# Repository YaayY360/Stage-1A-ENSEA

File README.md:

# Stage-1A-ENSEA
Project de gestion d'inventaire avec un lecteur de tag RFID et de la gestion de base de données

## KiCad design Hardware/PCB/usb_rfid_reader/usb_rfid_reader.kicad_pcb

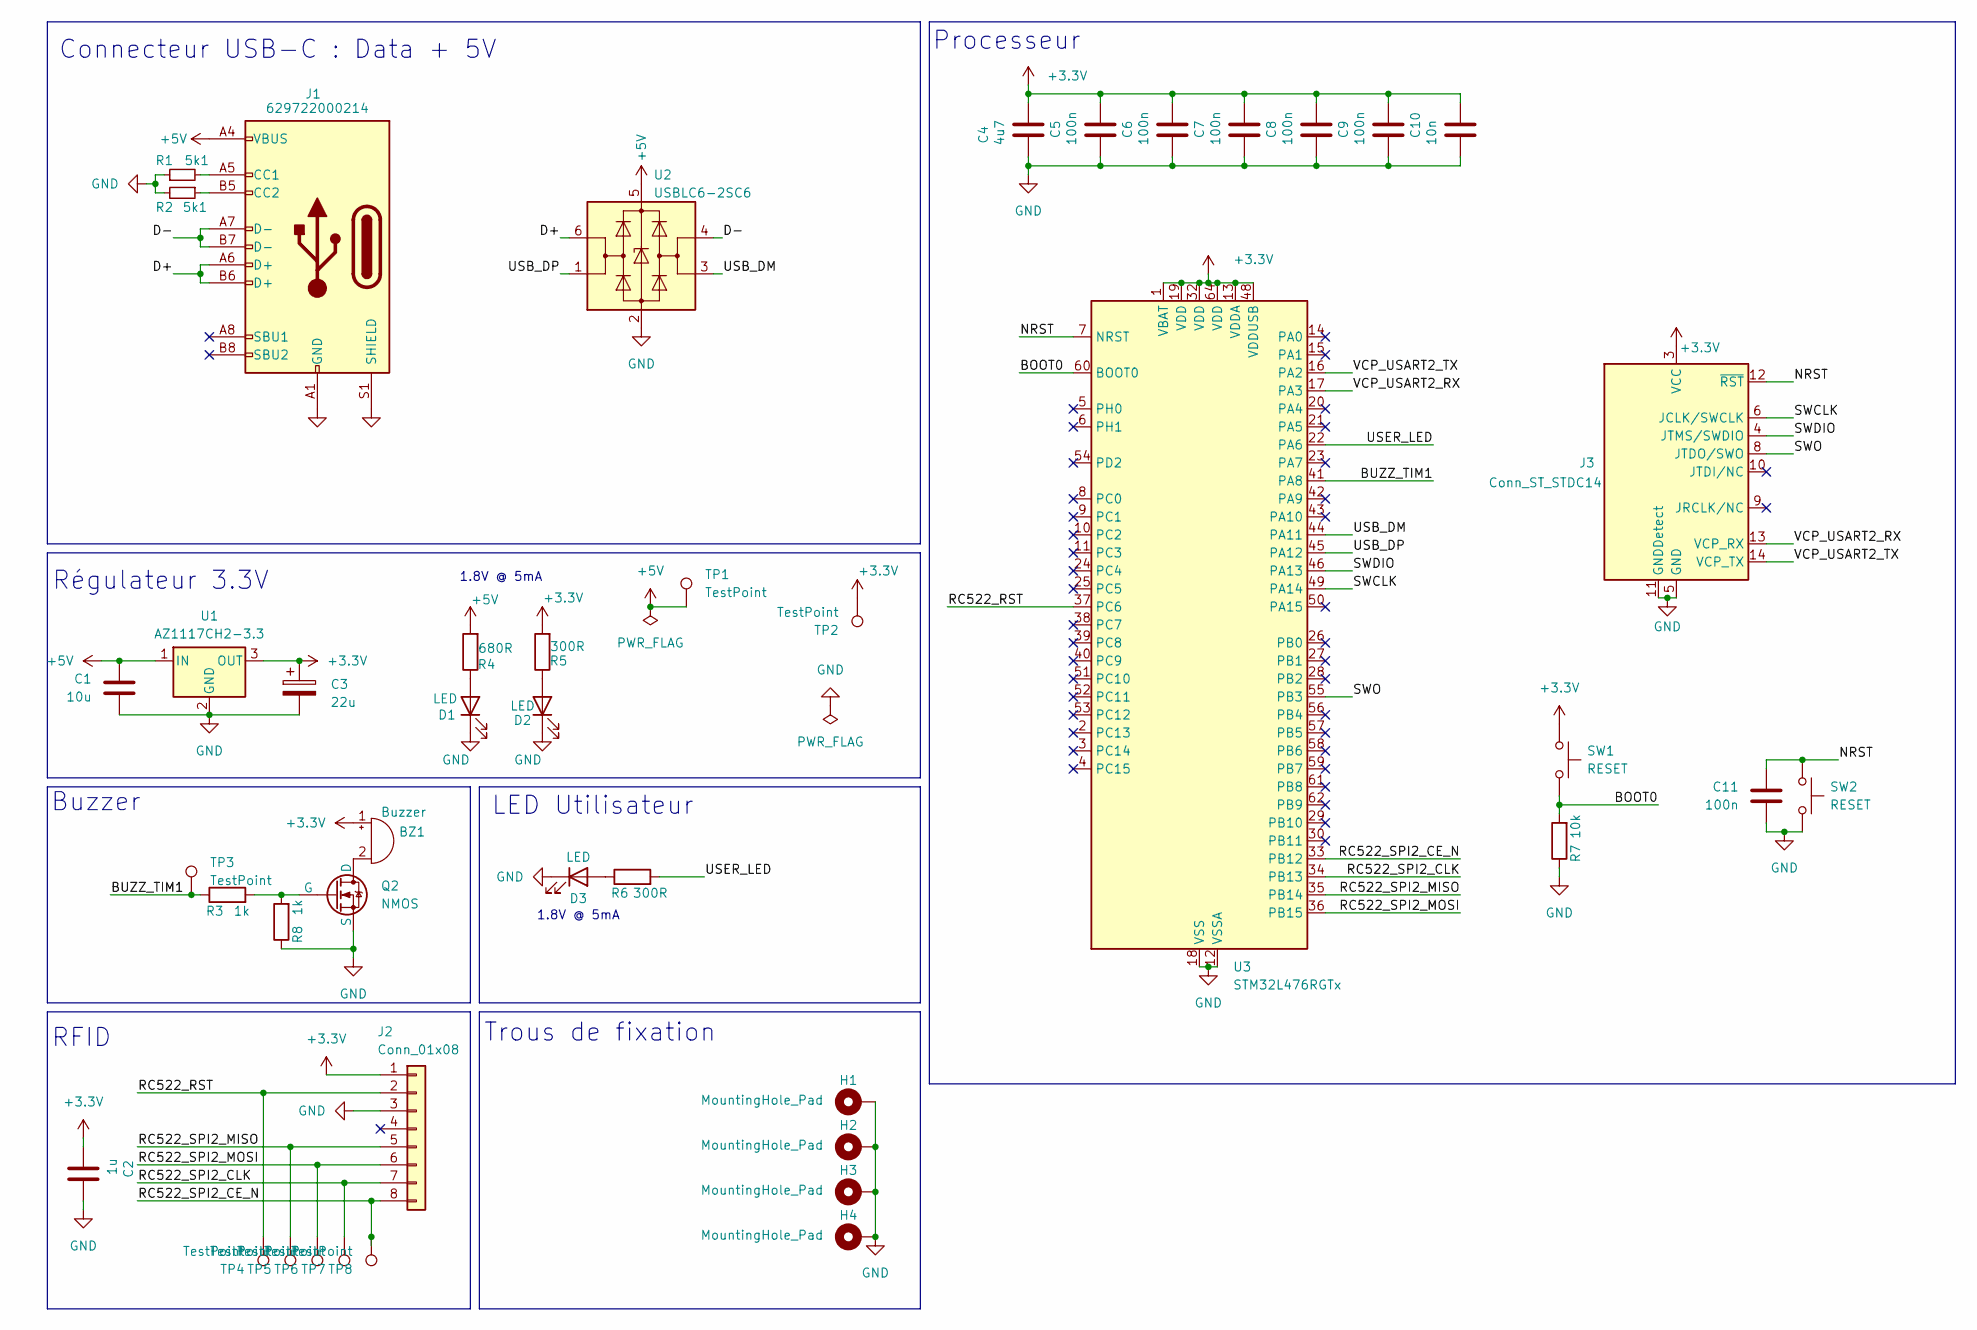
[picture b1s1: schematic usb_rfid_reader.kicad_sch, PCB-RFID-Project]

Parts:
BZ1: Buzzer; Buzzer_D14mm_H7mm_P10mm; MPN PS1420P02CT
C1: 10u; C_0603_1608Metric; MPN 885012106031
C2: 1u; C_0603_1608Metric; MPN GRM188R61A475KE15D
C3: 22u; CP_Elec_5x5.4; MPN 865060442002
C4: 4u7; C_0603_1608Metric; MPN GRM188R61A475KE15D
C5, C6, C7, C8, C9, C11: 100n; C_0603_1608Metric; MPN GRM188R71C104KA01D
C10: 10n; C_0603_1608Metric; MPN GRM188R71C104KA01D
D1, D2, D3: LED; LED_0603_1608Metric; MPN 150060RS55040
H1, H2, H3, H4: MountingHole_Pad; MountingHole_3.2mm_M3_DIN965_Pad
J1: 629722000214; USB_C_Receptacle_HRO_TYPE-C-31-M-12; MPN WE 629722000214
J2: Conn_01x08; MODULE_CEG006900; MPN 61300811121
J3: Conn_ST_STDC14; PinHeader_2x07_P1.27mm_Vertical_SMD; MPN STDC14
Q2: NMOS; SOT-23-3; MPN SQ2310ES-T1_BE3
R1, R2: 5k1; R_0402_1005Metric
R3, R8: 1k; R_0603_1608Metric; MPN RC0603FR-071KL
R4: 680R; R_0603_1608Metric; MPN RC0603FR-073KL
R5, R6: 300R; R_0603_1608Metric; MPN RC0603FR-071K5L
R7: 10k; R_0603_1608Metric; MPN RC0603FR-0710KL
SW1, SW2: RESET; SW_SPST_PTS645Sx43SMTR92; MPN PTS645SK43SMTR92 LFS
TP1, TP2, TP3, TP4, TP5, TP6, TP7, TP8: TestPoint; TestPoint_Pad_D1.0mm
U1: AZ1117CH2-3.3; SOT-223-3_TabPin2; MPN AZ1117CH2-3.3TRG1
U2: USBLC6-2SC6; SOT-23-6; MPN USBLC6-2SC6
U3: STM32L476RGTx; LQFP-64_10x10mm_P0.5mm; MPN STM32L476RGT6

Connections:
+3.3V: BZ1.1 (+), C2.1, C3.1, C4.2, C5.2, C6.2, C7.2, C8.2, C9.2, C10.2, J2.1, J3.3 (VCC), R5.2, SW1.1, TP2.1, U1.3 (OUT), U3.1 (VBAT), U3.13 (VDDA), U3.19 (VDD), U3.32 (VDD), U3.48 (VDDUSB), U3.64 (VDD)
+5V: C1.1, J1.A4 (VBUS), J1.A9 (VBUS), J1.B4 (VBUS), J1.B9 (VBUS), R4.2, TP1.1, U1.1 (IN), U2.5 (VBUS)
/BOOT0: R7.2, SW1.2, U3.60 (BOOT0)
/BUZZ_TIM1: R3.1, TP3.1, U3.41 (PA8)
/D+: J1.A6 (D+), J1.B6 (D+), U2.6 (I/O1)
/D-: J1.A7 (D-), J1.B7 (D-), U2.4 (I/O2)
/NRST: C11.1, J3.12 (~RST), SW2.1, U3.7 (NRST)
/RC522_RST: J2.2, TP4.1, U3.37 (PC6)
/RC522_SPI2_CE_N: J2.8, TP8.1, U3.33 (PB12)
/RC522_SPI2_CLK: J2.7, TP7.1, U3.34 (PB13)
/RC522_SPI2_MISO: J2.5, TP5.1, U3.35 (PB14)
/RC522_SPI2_MOSI: J2.6, TP6.1, U3.36 (PB15)
/SWCLK: J3.6 (JCLK/SWCLK), U3.49 (PA14)
/SWDIO: J3.4 (JTMS/SWDIO), U3.46 (PA13)
/SWO: J3.8 (JTDO/SWO), U3.55 (PB3)
/USB_DM: U2.3 (I/O2), U3.44 (PA11)
/USB_DP: U2.1 (I/O1), U3.45 (PA12)
/USER_LED: R6.2, U3.22 (PA6)
/VCP_USART2_RX: J3.13 (VCP_RX), U3.17 (PA3)
/VCP_USART2_TX: J3.14 (VCP_TX), U3.16 (PA2)
GND: C1.2, C2.2, C3.2, C4.1, C5.1, C6.1, C7.1, C8.1, C9.1, C10.1, C11.2, D1.1 (K), D2.1 (K), D3.1 (K), H1.1, H2.1, H3.1, H4.1, J1.A1 (GND), J1.A12 (GND), J1.B1 (GND), J1.B12 (GND), J1.S1 (SHIELD), J2.3, J3.5 (GND), J3.7 (GND), J3.11 (GNDDetect), Q2.3 (S), R1.1, R2.2, R7.1, R8.1, SW2.2, U1.2 (GND), U2.2 (GND), U3.12 (VSSA), U3.18 (VSS), U3.31 (VSS), U3.47 (VSS), U3.63 (VSS)
unnamed: BZ1.2 (-), Q2.1 (D)
unnamed: D1.2 (A), R4.1
unnamed: D2.2 (A), R5.1
unnamed: D3.2 (A), R6.1
unnamed: J1.A5 (CC1), R1.2
unnamed: J1.B5 (CC2), R2.1
unnamed: Q2.2 (G), R3.2, R8.2

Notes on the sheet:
1.8V @ 5mA
Processeur
LED Utilisateur
RFID
Trous de fixation
Régulateur 3.3V
Buzzer
Connecteur USB-C : Data + 5V

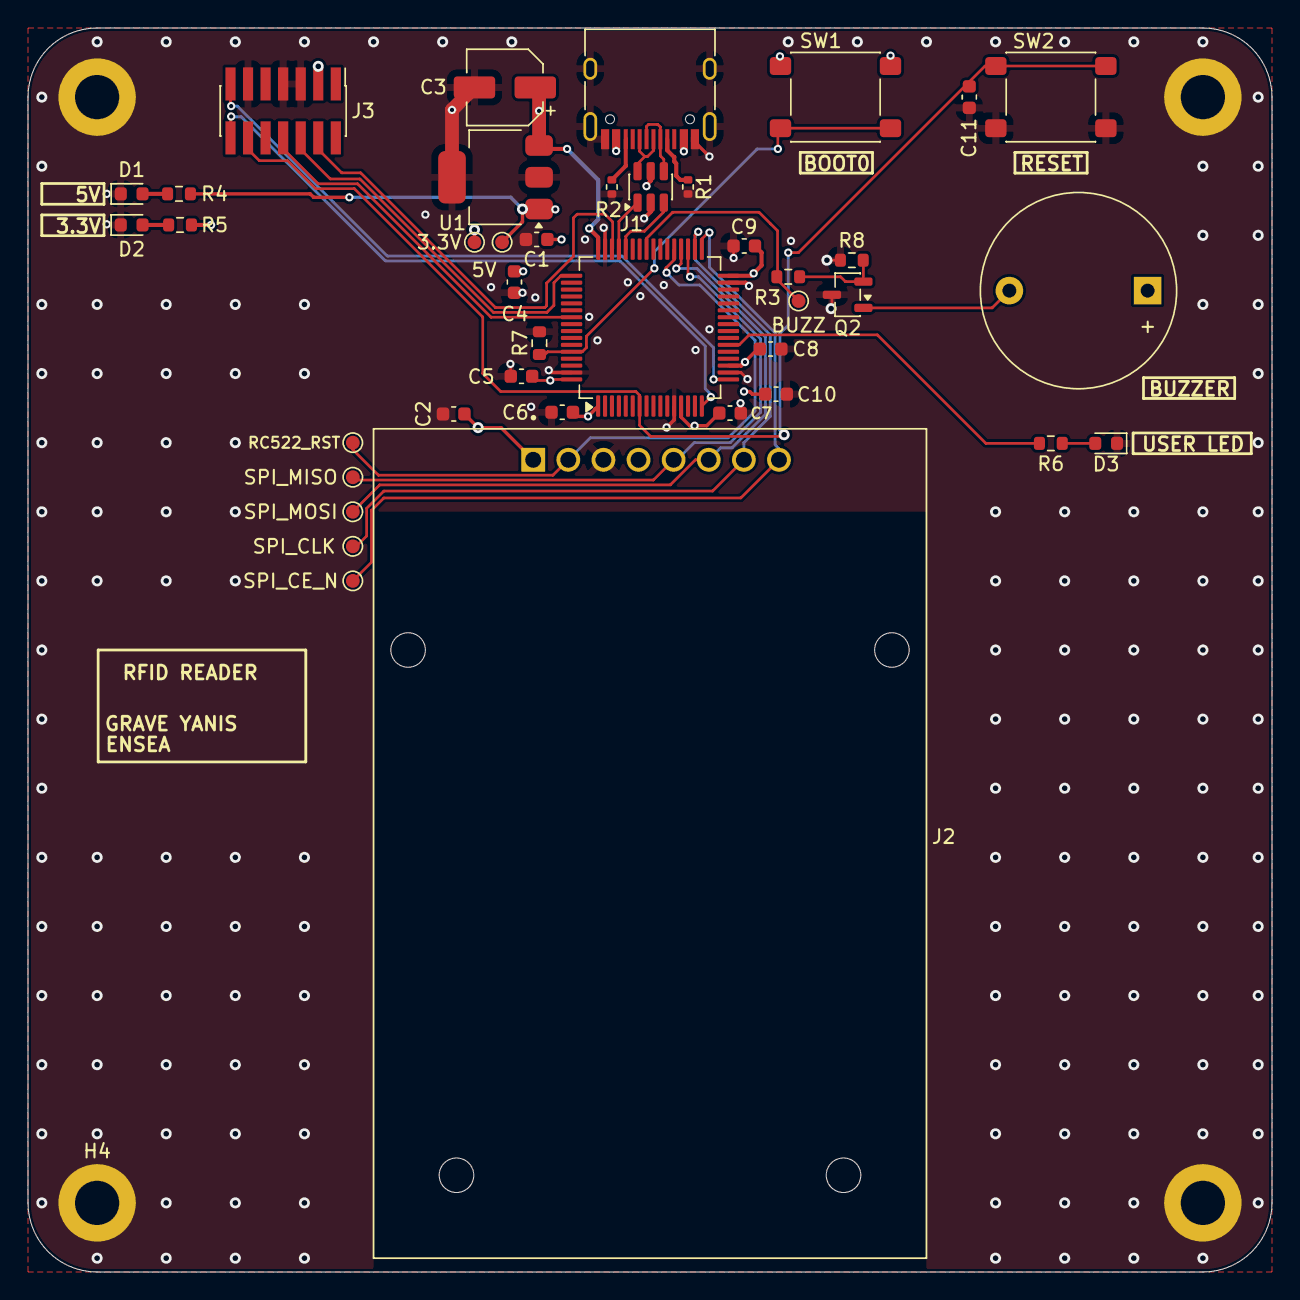
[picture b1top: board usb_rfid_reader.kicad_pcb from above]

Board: 4 copper layers, 90.0 x 90.0 mm, 44 parts (0 on the bottom side), 28 nets.

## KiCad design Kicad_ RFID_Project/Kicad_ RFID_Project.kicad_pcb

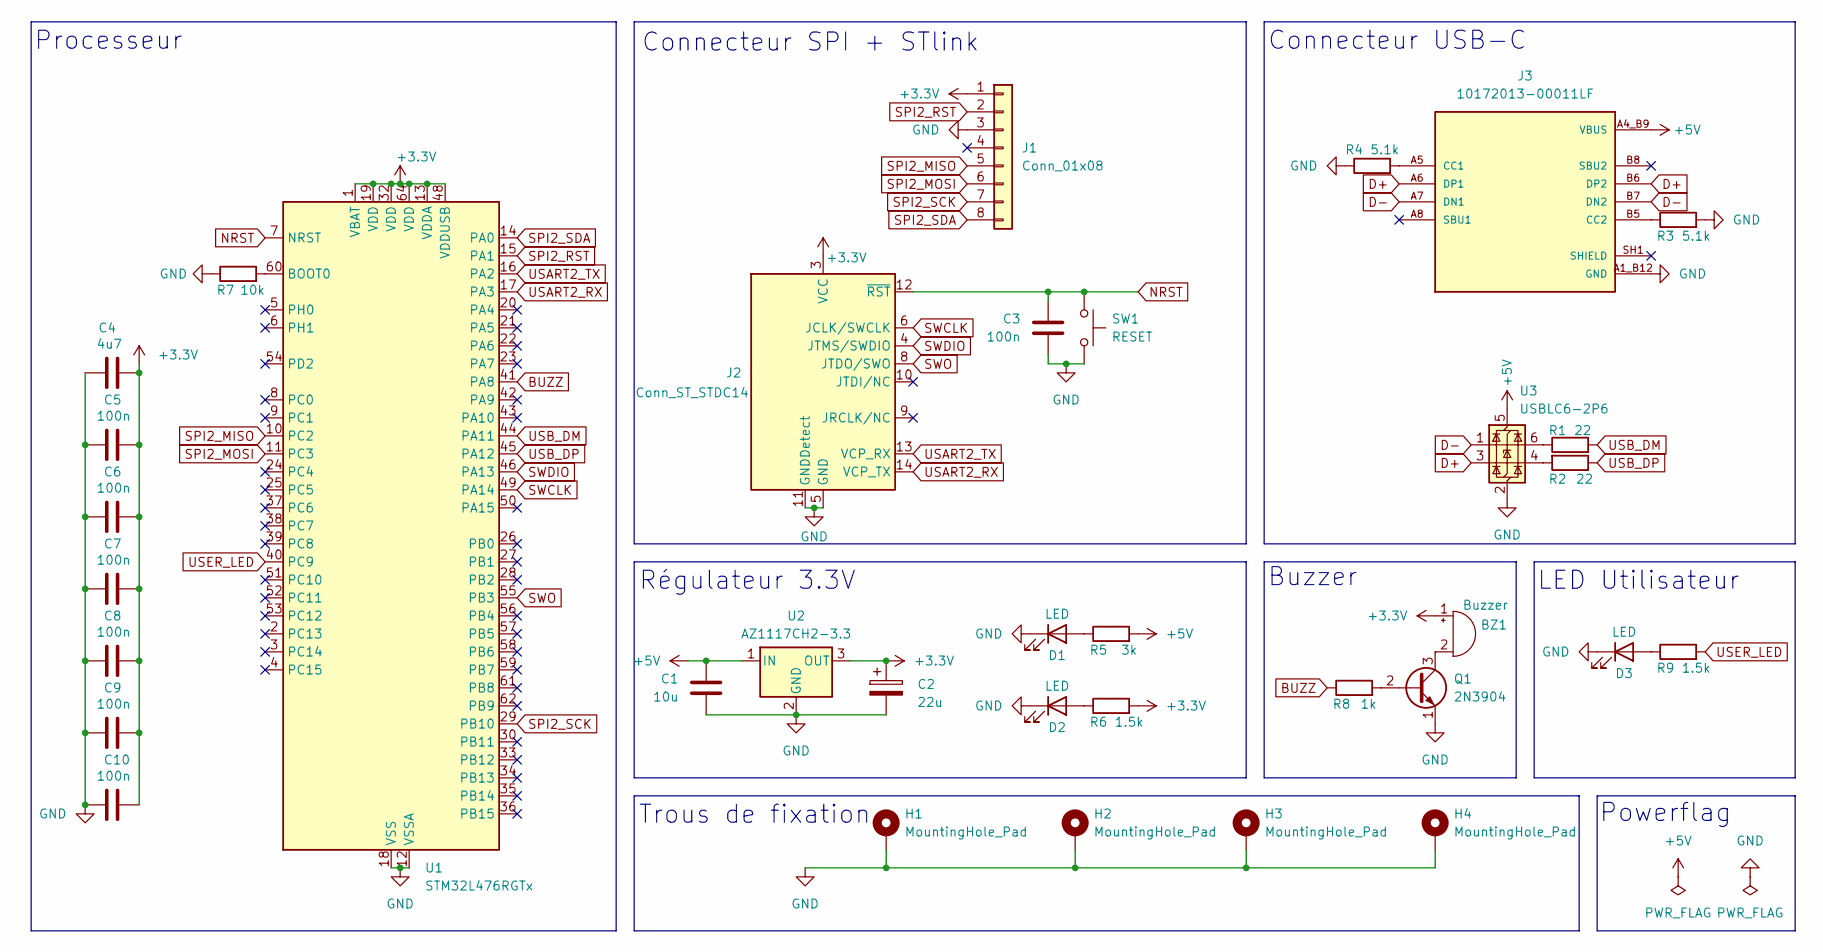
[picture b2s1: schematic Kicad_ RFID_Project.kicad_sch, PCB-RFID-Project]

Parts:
BZ1: Buzzer; Buzzer_D14mm_H7mm_P10mm; MPN PS1420P02CT
C1: 10u; C_0603_1608Metric; MPN GRM188R61A106KE69D
C2: 22u; CP_Elec_5x5.4; MPN GRM21BR61A226ME44L
C3, C5, C6, C7, C8, C9, C10: 100n; C_0603_1608Metric; MPN GRM188R71C104KA01D
C4: 4u7; C_0603_1608Metric; MPN GRM188R61A475KE15D
D1, D2, D3: LED; LED_0603_1608Metric; MPN 150060RS75000
H1, H2, H3, H4: MountingHole_Pad; MountingHole_3.2mm_M3_DIN965_Pad
J1: Conn_01x08; MODULE_CEG006900; MPN 61300811121
J2: Conn_ST_STDC14; PinHeader_2x07_P1.27mm_Vertical_SMD; MPN STDC14
J3: 10172013-00011LF; AMPHENOL_10172013-00011LF; PARTREV A
Q1: 2N3904; TO-92_Inline; MPN 2N3904BU
R1, R2: 22; R_0603_1608Metric; MPN RC0603FR-0722RL
R3, R4: 5.1k; R_0603_1608Metric; MPN RC0603FR-0722RL
R5: 3k; R_0603_1608Metric; MPN RC0603FR-073KL
R6, R9: 1.5k; R_0603_1608Metric; MPN RC0603FR-071K5L
R7: 10k; R_0603_1608Metric; MPN RC0603FR-0710KL
R8: 1k; R_0603_1608Metric; MPN RC0603FR-071KL
SW1: RESET; SW_SPST_PTS645Sx43SMTR92; MPN PTS645SK43SMTR92 LFS
U1: STM32L476RGTx; LQFP-64_10x10mm_P0.5mm; MPN STM32L476RGT6
U2: AZ1117CH2-3.3; SOT-223-3_TabPin2; MPN AZ1117CH2-3.3TRG1
U3: USBLC6-2P6; SOT-666; MPN USBLC6-2P6

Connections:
+3.3V: BZ1.1 (+), C2.1, C4.2, C5.2, C6.2, C7.2, C8.2, C9.2, C10.2, J1.1, J2.3 (VCC), R6.2, U1.1 (VBAT), U1.13 (VDDA), U1.19 (VDD), U1.32 (VDD), U1.48 (VDDUSB), U1.64 (VDD), U2.3 (OUT)
+5V: C1.1, J3.A4_B9 (VBUS), J3.A9_B4 (VBUS), R5.2, U2.1 (IN), U3.5 (VBUS)
BUZZ: R8.1, U1.41 (PA8)
D+: J3.A6 (DP1), J3.B6 (DP2), U3.3 (I/O2)
D-: J3.A7 (DN1), J3.B7 (DN2), U3.1 (I/O1)
GND: C1.2, C2.2, C3.2, C4.1, C5.1, C6.1, C7.1, C8.1, C9.1, C10.1, D1.1 (K), D2.1 (K), D3.1 (K), H1.1, H2.1, H3.1, H4.1, J1.3, J2.5 (GND), J2.7 (GND), J2.11 (GNDDetect), J3.A1_B12 (GND), J3.A12_B1 (GND), Q1.1 (E), R3.2, R4.1, R7.1, SW1.2, U1.12 (VSSA), U1.18 (VSS), U1.31 (VSS), U1.47 (VSS), U1.63 (VSS), U2.2 (GND), U3.2 (GND)
NRST: C3.1, J2.12 (~RST), SW1.1, U1.7 (NRST)
unnamed: BZ1.2 (-), Q1.3 (C)
unnamed: D1.2 (A), R5.1
unnamed: D2.2 (A), R6.1
unnamed: D3.2 (A), R9.1
unnamed: J3.A5 (CC1), R4.2
unnamed: J3.B5 (CC2), R3.1
unnamed: Q1.2 (B), R8.2
unnamed: R1.1, U3.6 (I/O1)
unnamed: R2.2, U3.4 (I/O2)
unnamed: R7.2, U1.60 (BOOT0)
SPI2_MISO: J1.5, U1.10 (PC2)
SPI2_MOSI: J1.6, U1.11 (PC3)
SPI2_RST: J1.2, U1.15 (PA1)
SPI2_SCK: J1.7, U1.29 (PB10)
SPI2_SDA: J1.8, U1.14 (PA0)
SWCLK: J2.6 (JCLK/SWCLK), U1.49 (PA14)
SWDIO: J2.4 (JTMS/SWDIO), U1.46 (PA13)
SWO: J2.8 (JTDO/SWO), U1.55 (PB3)
USART2_RX: J2.14 (VCP_TX), U1.17 (PA3)
USART2_TX: J2.13 (VCP_RX), U1.16 (PA2)
USB_DM: R1.2, U1.44 (PA11)
USB_DP: R2.1, U1.45 (PA12)
USER_LED: R9.2, U1.40 (PC9)

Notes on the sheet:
Processeur
LED Utilisateur
Powerflag
Régulateur 3.3V
Connecteur SPI + STlink
Trous de fixation
Buzzer
Connecteur USB-C

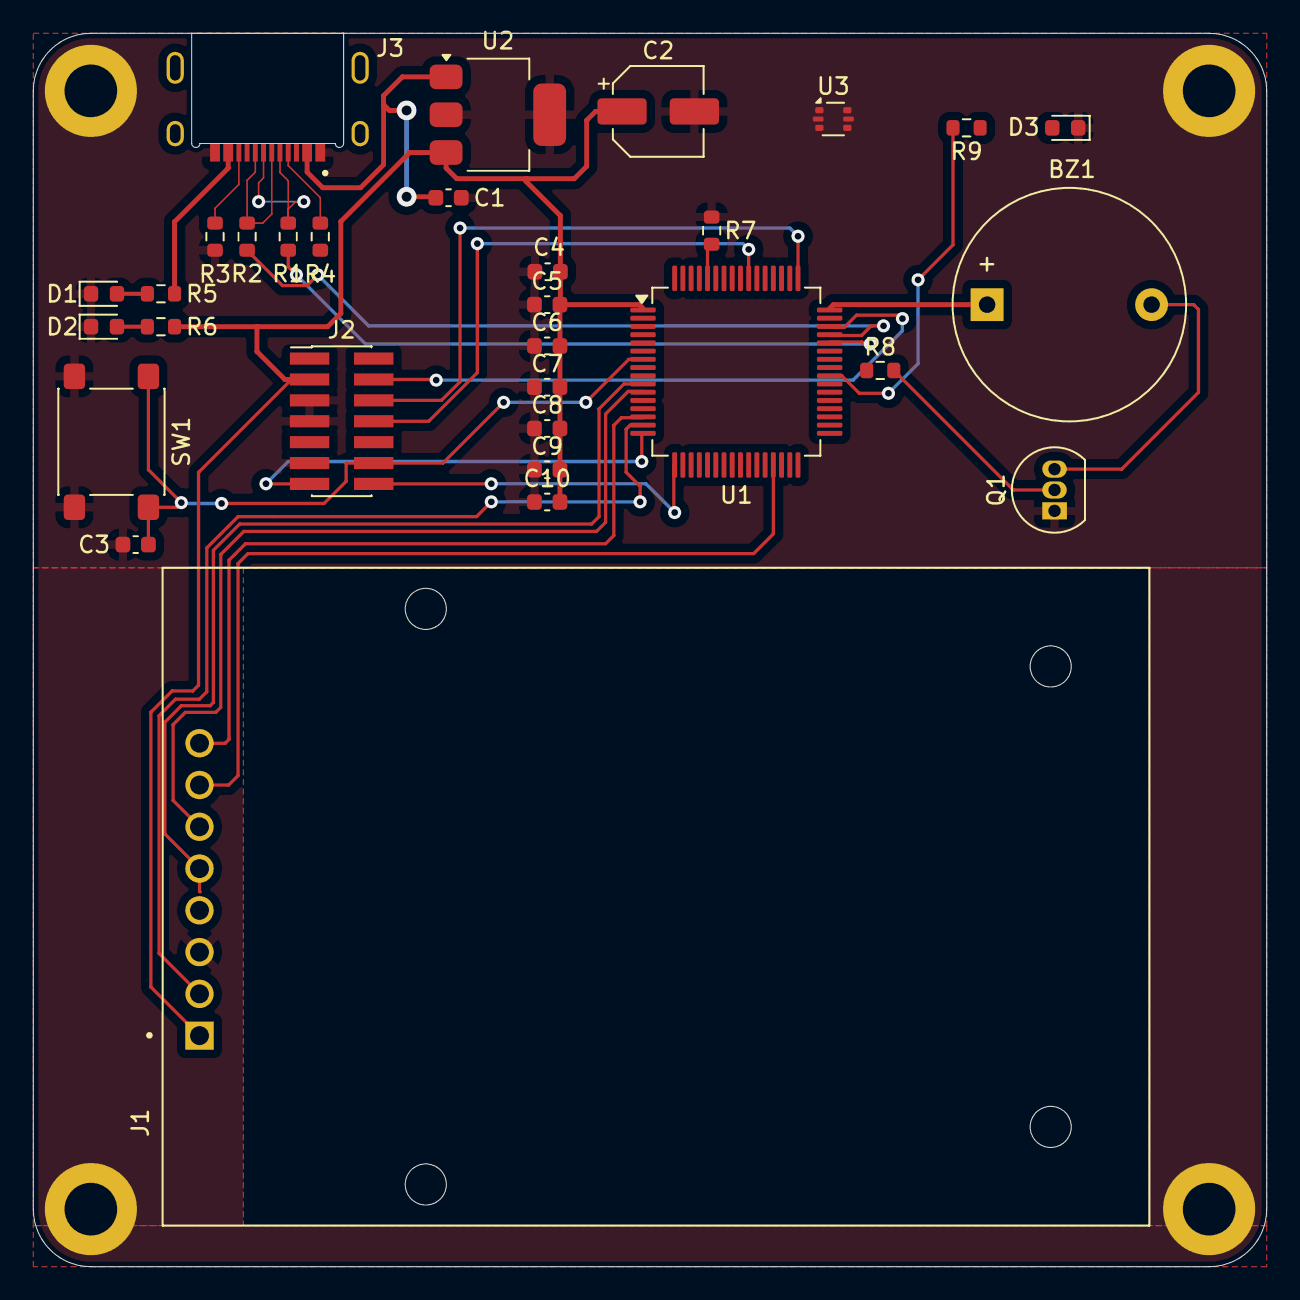
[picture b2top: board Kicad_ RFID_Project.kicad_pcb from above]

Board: 2 copper layers, 75.0 x 75.0 mm, 35 parts (0 on the bottom side), 30 nets.

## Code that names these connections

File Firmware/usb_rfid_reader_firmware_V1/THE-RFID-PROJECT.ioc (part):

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Mcu.Name=STM32L476R(C-E-G)Tx
Mcu.Package=LQFP64
Mcu.UserName=STM32L476RGTx
PA11.Mode=Device_Only
PA11.Signal=USB_OTG_FS_DM
PA12.Mode=Device_Only
PA12.Signal=USB_OTG_FS_DP
PA13\ (JTMS-SWDIO).Mode=Trace_Asynchronous_SW
PA13\ (JTMS-SWDIO).Signal=SYS_JTMS-SWDIO
PA14\ (JTCK-SWCLK).Mode=Trace_Asynchronous_SW
PA14\ (JTCK-SWCLK).Signal=SYS_JTCK-SWCLK
PA2.Mode=Asynchronous
PA2.Signal=USART2_TX
PA3.Mode=Asynchronous
PA3.Signal=USART2_RX
PA6.GPIOParameters=GPIO_Label
PA6.GPIO_Label=LED
PA6.Signal=GPIO_Output
PA8.GPIOParameters=GPIO_Label
PA8.GPIO_Label=BUZZ_TIM1
PA8.Signal=S_TIM1_CH1
PB12.Mode=NSS_Signal_Hard_Output
PB12.Signal=SPI2_NSS
PB13.Mode=Full_Duplex_Master
PB13.Signal=SPI2_SCK
PB14.Mode=Full_Duplex_Master
PB14.Signal=SPI2_MISO
PB15.Mode=Full_Duplex_Master
PB15.Signal=SPI2_MOSI
PB3\ (JTDO-TRACESWO).Mode=Trace_Asynchronous_SW
PB3\ (JTDO-TRACESWO).Signal=SYS_JTDO-SWO
PC6.GPIOParameters=GPIO_Label
PC6.GPIO_Label=RC522_RST
PC6.Signal=GPIO_Output
PH0-OSC_IN\ (PH0).Mode=HSE-External-Oscillator
PH0-OSC_IN\ (PH0).Signal=RCC_OSC_IN
PH1-OSC_OUT\ (PH1).Mode=HSE-External-Oscillator
PH1-OSC_OUT\ (PH1).Signal=RCC_OSC_OUT
RCC.HSE_VALUE=16000000
RCC.SYSCLKFreq_VALUE=80000000
RCC.SYSCLKSource=RCC_SYSCLKSOURCE_PLLCLK
board=custom

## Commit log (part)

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2026-06-02 ajout documentation
2026-06-03 ajout du schéma des pins de la nucélo
2026-06-03 ajout des fichiers Kicad
2026-06-03 ajout schéma Kicad
2026-06-03 changement kicad
2026-06-03 ajout trous de fixation kicad
2026-06-04 ajout mounting holes et powerflag
2026-06-05 derniers details schéma + début routage
2026-06-07 ajout des leds electrostatiques pour l'USB-C
2026-06-08 ajout datasheet LED ESD
2026-06-08 update directory / gitignore
2026-06-08 create directory
2026-06-08 review schematic
2026-06-08 modification labels
2026-06-08 corrections schéma
2026-06-08 ajout projet STM32cubeIDE
2026-06-08 ajout de l'environnement virtuel Django
2026-06-08 Initialisation du projet Django
2026-06-08 modification classes jango
2026-06-08 routage PCB avant ERC
2026-06-09 correctif erreur routage
2026-06-09 Ajout commentaires silkscreen PCB
2026-06-09 Création script API moussr
2026-06-09 ajout du schéma de principe du projet
2026-06-09 Correctifs japonais
2026-06-09 correctifs japonais 2
2026-06-10 correctifs japonais V3
2026-06-11 ajout modèle 3D socle + dernière modif PCB
2026-06-11 ajout des fichier gerber
2026-06-12 modifications software
2026-06-12 modification affichage drawer et tiroclass
2026-06-16 ajout base de donnée format ods
2026-06-17 modification base de donnée
2026-06-18 modification interface de recherche composant
2026-06-18 dernière modfis menu déroulants
2026-06-18 modification cybersécurité
2026-06-18 dernières modification système d'API
2026-06-22 ajour modèle 3D socle
2026-06-24 ajout authentification, liste composant actuels et filtrage
2026-06-25 Ia de classification fonctionnel
2026-06-28 correction mineures
